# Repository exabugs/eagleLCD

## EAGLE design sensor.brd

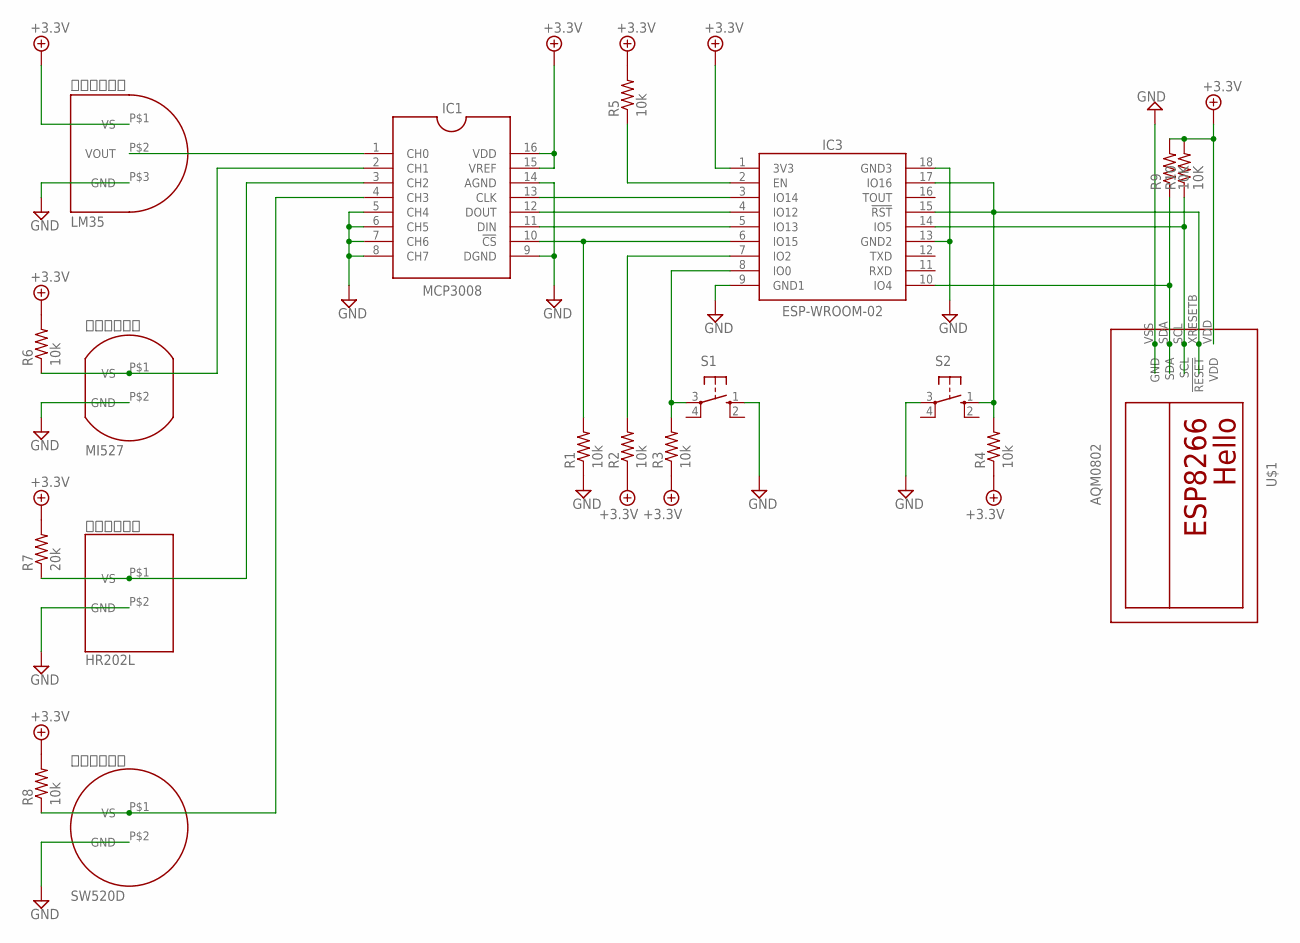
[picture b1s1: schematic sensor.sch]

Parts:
IC1: MCP3008; DIL16
IC3: ESP-WROOM-02; WROOM-02
R1, R2, R3, R4, R5, R6, R8: 10k; 0309/12
R7: 20k; 0309/12
R9, R10: 10K; 0309/12
S1, S2: 10-XX(タクトスイッチ); B3F-10XX
U$1: AQM0802
振動センサー: SW520D; SW520D(振動センサー)
温度センサー: LM35
湿度センサー: HR202L
照度センサー: MI527; MI527(照度センサー)

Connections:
+3.3V: IC1.15 (VREF), IC1.16 (VDD), IC3.1 (3V3), R2.1, R3.1, R4.1, R5.2, R6.2, R7.2, R8.2, R9.2, R10.2, U$1.VDD, 温度センサー.P$1 (VS)
AGND: IC1.9 (DGND), IC1.14 (AGND)
GND: IC1.5 (CH4), IC1.6 (CH5), IC1.7 (CH6), IC1.8 (CH7), R1.1, S1.1 (S), S2.3, U$1.VSS (GND), 振動センサー.P$2 (GND), 温度センサー.P$3 (GND), 湿度センサー.P$2 (GND), 照度センサー.P$2 (GND)
GND1: IC3.9 (GND1)
GND3: IC3.13 (GND2), IC3.18 (GND3)
unnamed: IC1.10 (!CS!), IC3.6 (IO15), R1.2
unnamed: IC1.11 (DIN), IC3.5 (IO13)
unnamed: IC1.12 (DOUT), IC3.4 (IO12)
unnamed: IC3.7 (IO2), R2.2
unnamed: IC1.2 (CH1), R6.1, 照度センサー.P$1 (VS)
unnamed: IC1.13 (CLK), IC3.3 (IO14)
unnamed: IC3.15 (!RST!), IC3.17 (IO16), R4.2, S2.1 (S), U$1.XRESETB (!RESET!)
unnamed: IC3.8 (IO0), R3.2, S1.3
unnamed: IC1.1 (CH0), 温度センサー.P$2 (VOUT)
unnamed: IC1.3 (CH2), R7.1, 湿度センサー.P$1 (VS)
unnamed: IC1.4 (CH3), R8.1, 振動センサー.P$1 (VS)
unnamed: IC3.14 (IO5), R10.1, U$1.SCL
unnamed: IC3.2 (EN), R5.1
unnamed: IC3.10 (IO4), R9.1, U$1.SDA

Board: 2 copper layers, 19 parts (0 on the bottom side), 18 nets, no tracks yet.

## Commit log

2016-01-24 First Commit.
2016-01-30 commit.
